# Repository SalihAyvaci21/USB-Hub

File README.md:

# USB Hub + PD Controller Projesi

Bu proje, USB-C PD (Power Delivery) desteği ile çalışan, 5V-24V arası giriş voltajını kabul eden ve gücü dört farklı çıkışa dağıtan bir **USB Hub** tasarımıdır. Güç ve sinyal yönetimi için çeşitli koruma ve anahtarlama IC’leri entegre edilmiştir.

## 📦 Özellikler

- **Giriş Voltajı (USB-C):** 5V - 24V (PD destekli)
- **Çıkışlar:**
  - 1x **USB-A 3.0**
  - 1x **USB-C 3.0**
  - 1x **FTDI (UART-USB dönüştürücü)**
  - 1x **ST-Link (Programlayıcı / Debugger)**
- **PD Controller:** CH224K (Switch ile kontrol)
- **USB Hub IC:** TUSB8044ARGCR
- **Sinyal Yönlendirme:**
  - 2x HD3SS3202IRSVR (SS MUX, C-to-A ve A-to-C için)
- **Koruma Devreleri:**
  - TPD6S300A (ESD ve güç koruması)
- **Güç Regülasyonu:**
  - 1.1V: TLV71211 (SOT23-5)
  - 3.3V: NCP1117-3.3 (SOT-223)
  - 5V: KA78M05 (TO-252)
- **Programlayıcılar:**
  - ST-Link için STM32F103CBTx
  - FTDI için FT232RL-REEL

## 🛠 Bileşenler

| Bileşen                  | Açıklama                        |
|-------------------------|------------------------------------|
| **CH224K**              | USB-C PD Controller              |
| **TUSB8044ARGCR**       | USB 3.0 Hub Controller            |
| **HD3SS3202IRSVR**      | USB SS MUX (C/A anahtarlama)      |
| **TPD6S300A**           | USB-C koruma (ESD, VBUS)          |
| **TLV71211**            | 1.1V LDO Regülatör                |
| **NCP1117-3.3**         | 3.3V LDO Regülatör                |
| **KA78M05**             | 5V Regülatör                      |
| **STM32F103CBTx**       | ST-Link Programlayıcı MCU         |
| **FT232RL-REEL**        | FTDI USB-UART dönüştürücü         |

## 📐 Tasarım Özellikleri

- **PD Desteği:** 5V ila 24V arası giriş voltajını otomatik algılar entegre doğru çıkışı verir.
- **Güç Dağıtımı:** TUSB8044ARGCR ile USB 3.0 sinyalleri dört porta bölünür.
- **Sinyal Yönlendirme:** HD3SS3202 ile USB-C ve USB-A arasında yüksek hızlı sinyal yönlendirme.
- **Güvenlik:** TPD6S300A ile USB-C girişinde aşırı gerilim ve ESD koruması.
- **Programlama ve Debug:** Dahili ST-Link (STM32F103CBTx) ve FTDI (FT232RL) arayüzleri.

## 🔌 Kullanım

1. **Giriş Bağlantısı:**
   - USB-C PD girişine adaptör bağlayın (5V-24V arası desteklenir).
2. **Çıkışlar:**
   - USB-A 3.0 portuna cihaz bağlanabilir.
   - USB-C 3.0 portu yüksek hızlı veri aktarımı için kullanılabilir.
   - FTDI portu UART bağlantısı için kullanılabilir.
   - ST-Link portu STM32 debug/programlama için hazırdır.

## ⚡ Koruma ve Güvenlik

- **ESD Koruma:** TPD6S300A
- **Aşırı Gerilim:** PD kontrolcü ile voltaj sınırlaması
- **Sinyal Integrity:** SS MUX ile minimum sinyal kaybı

## 📁 Dosyalar

- `Usb 3. v11.kicad_pro` – KiCAD proje dosyası
- `Usb 3. v11.kicad_sch` – Devre şeması
- `gerber` – Üretim için Gerber dosyaları 
- `BomList.xlsx` – Parça listesi

## ⚠️ Dikkat

> Bu tasarım yüksek hızlı USB sinyalleri ve PD voltajları içerir. Geliştirme ve test sırasında uygun yalıtım ve ESD önlemleri alınmalıdır.

## 📜 Lisans

Bu proje açık kaynaklıdır ve kişisel/akademik kullanım için serbesttir.

---

# USB Hub + PD Controller Project

This project is a **USB Hub** design that operates with USB-C PD (Power Delivery) support, accepting an input voltage range of 5V-24V and distributing power across four different outputs. Various protection and switching ICs are integrated for power and signal management.

## 📦 Features

- **Input Voltage (USB-C):** 5V - 24V (PD supported)
- **Outputs:**
  - 1x **USB-A 3.0**
  - 1x **USB-C 3.0**
  - 1x **FTDI (UART-USB converter)**
  - 1x **ST-Link (Programmer / Debugger)**
- **PD Controller:** CH224K (controlled via switch)
- **USB Hub IC:** TUSB8044ARGCR
- **Signal Routing:**
  - 2x HD3SS3202IRSVR (SS MUX for C-to-A and A-to-C)
- **Protection Circuits:**
  - TPD6S300A (ESD and power protection)
- **Power Regulation:**
  - 1.1V: TLV71211 (SOT23-5)
  - 3.3V: NCP1117-3.3 (SOT-223)
  - 5V: KA78M05 (TO-252)
- **Programmers:**
  - STM32F103CBTx for ST-Link
  - FT232RL-REEL for FTDI

## 🛠 Components

| Component              | Description                         |
|------------------------|-------------------------------------|
| **CH224K**             | USB-C PD Controller                 |
| **TUSB8044ARGCR**      | USB 3.0 Hub Controller              |
| **HD3SS3202IRSVR**     | USB SS MUX (C/A switching)          |
| **TPD6S300A**          | USB-C protection (ESD, VBUS)        |
| **TLV71211**           | 1.1V LDO Regulator                  |
| **NCP1117-3.3**        | 3.3V LDO Regulator                  |
| **KA78M05**            | 5V Regulator                        |
| **STM32F103CBTx**      | ST-Link Programmer MCU              |
| **FT232RL-REEL**       | FTDI USB-UART Converter             |

## 📐 Design Features

- **PD Support:** Automatically detects input voltage between 5V and 24V and provides appropriate regulated output.
- **Power Distribution:** USB 3.0 signals are distributed to four ports using TUSB8044ARGCR.
- **Signal Routing:** High-speed signal switching between USB-C and USB-A via HD3SS3202.
- **Protection:** Overvoltage and ESD protection on USB-C input using TPD6S300A.
- **Programming and Debugging:** Integrated ST-Link (STM32F103CBTx) and FTDI (FT232RL) interfaces.

## 🔌 Usage

1. **Input Connection:**
   - Connect an adapter to the USB-C PD input (supports 5V-24V).
2. **Outputs:**
   - USB-A 3.0 port can connect to devices.
   - USB-C 3.0 port supports high-speed data transfer.
   - FTDI port can be used for UART connections.
   - ST-Link port is ready for STM32 debugging/programming.

## ⚡ Protection and Safety

- **ESD Protection:** TPD6S300A
- **Overvoltage:** Voltage limitation via PD controller
- **Signal Integrity:** Minimal signal loss using SS MUX

## 📁 Files

- `Usb 3. v11.kicad_pro` – KiCAD project file
- `Usb 3. v11.kicad_sch` – Schematic file
- `gerber` – Gerber files for production
- `BomList.xlsx` – Bill of Materials

## ⚠️ Warning

> This design involves high-speed USB signals and PD voltages. Proper insulation and ESD precautions must be taken during development and testing.

## 📜 License

This project is open-source and free for personal and academic use.

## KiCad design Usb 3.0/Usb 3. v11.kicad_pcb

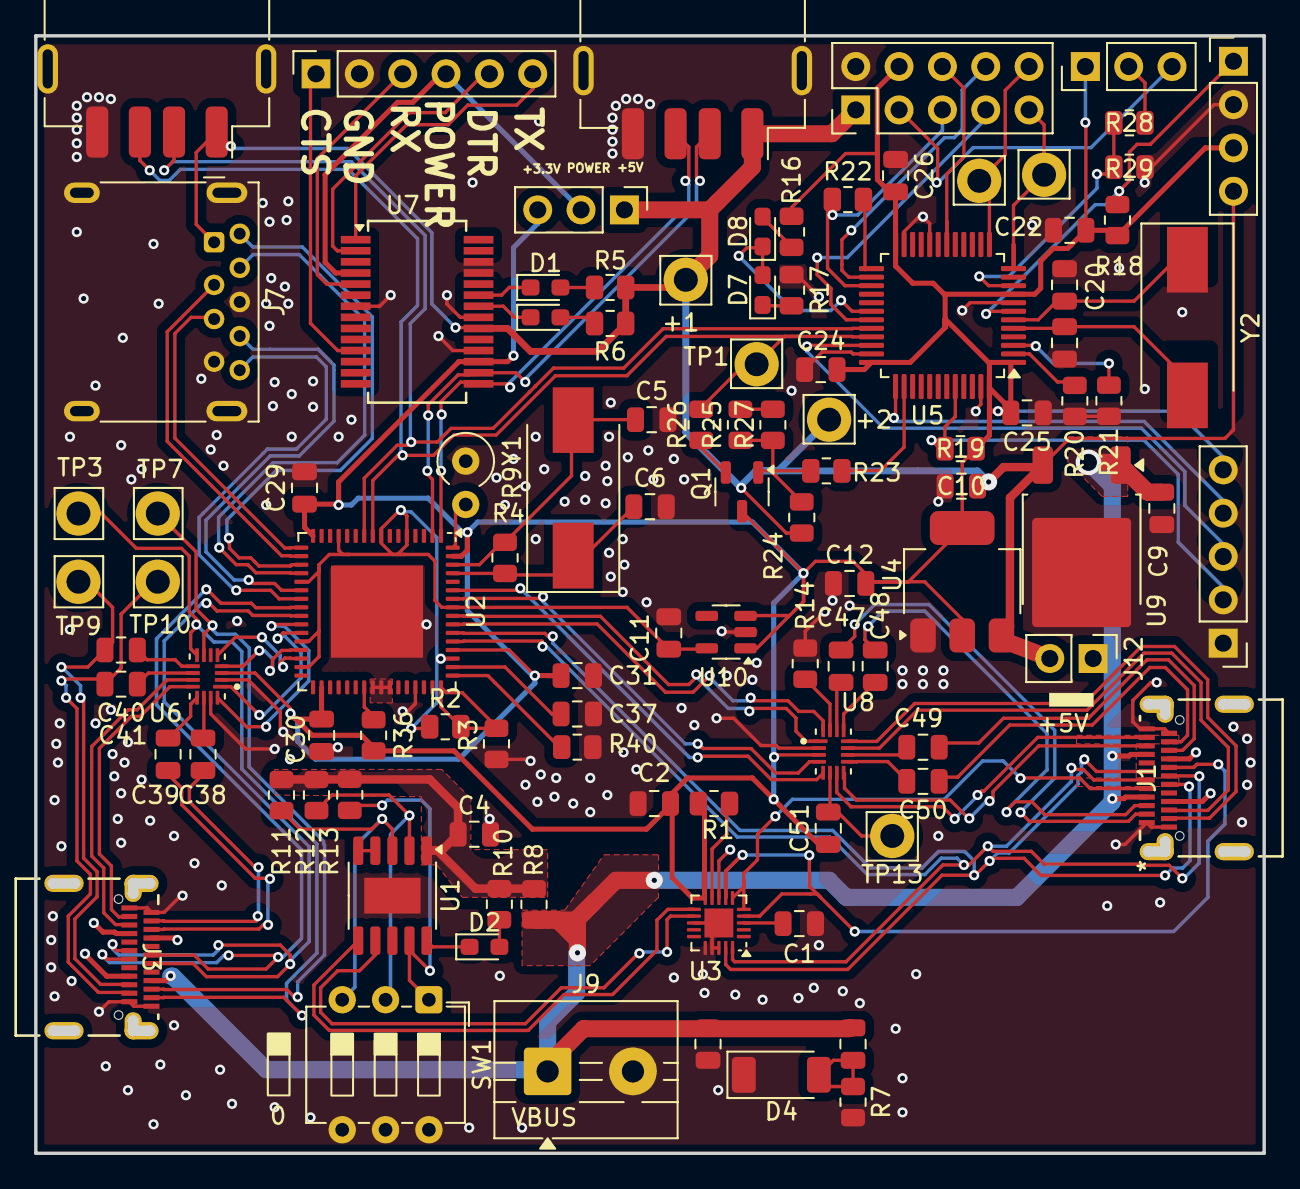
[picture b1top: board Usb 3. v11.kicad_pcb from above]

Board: 2 copper layers, 72.0 x 65.5 mm, 103 parts (0 on the bottom side), 108 nets.

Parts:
+1, +2: TestPoint; Pin_D1.4mm_L8.5mm_W2.8mm_FlatFork
C1, C29, C30, C31, C38, C39, C40, C41, C47, C48, C49, C50, C51: 0.1uF; C_0805_2012Metric
C2, C3, C4, C9, C10, C11, C12: 1uF; C_0805_2012Metric
C5, C6, C19, C20: 20pF; C_0805_2012Metric
C22, C24, C25, C26: 100nF; C_0805_2012Metric
C35: 4.7uF; C_0805_2012Metric
C37: 0.1uf; C_0805_2012Metric
D1, D3, D7, D8: LTST-C190GKT; LED_0603_1608Metric_Pad1.05x0.95mm_HandSolder
D2: LTST-C191KRKT; LED_0603_1608Metric_Pad1.05x0.95mm_HandSolder
D4: D_Schottky /20V/5A; D_SOD-128
J1, J3: KUSBX-SMT-CS2-B30TR; KUSBX-SMT3-CS-BTR_KYC
J2: Conn_01x06; PinSocket_1x06_P2.54mm_Vertical
J4: Conn_01x03_Pin; PinHeader_1x03_P2.54mm_Vertical
J5: Conn_01x05_Pin; PinHeader_1x05_P2.54mm_Vertical
J6: Conn_02x05_Odd_Even; PinHeader_2x05_P2.54mm_Vertical
J7: USB3_A; USB3_A_Molex_48393-001
J8, J10: USB_A; USB_A_Receptacle_GCT_USB1046
J9: Screw_Terminal_01x02; TerminalBlock_MaiXu_MX126-5.0-02P_1x02_P5.00mm
J11: Conn_01x04_Pin; PinHeader_1x04_P2.54mm_Vertical
J12: Screw_Terminal_01x02; PinHeader_1x02_P2.54mm_Vertical
JP1: SolderJumper_3_Open; PinHeader_1x03_P2.54mm_Vertical
Q1: BC817-25-TP; SOT-23-3
R1: 100k; R_0805_2012Metric
R2: 90.9k %1; R_0805_2012Metric
R3: 10k %1; R_0805_2012Metric
R4: 1M; R_0805_2012Metric
R5, R6, R8, R10, R16, R17: 1k; R_0805_2012Metric
R7: 3.5ohm; R_0805_2012Metric
R9: 0.53k %1; R_Axial_DIN0309_L9.0mm_D3.2mm_P2.54mm_Vertical
R11, R12, R13, R14, R18, R19, R36, R40: 10k; R_0805_2012Metric
R20, R21, R24: 10K; R_0805_2012Metric
R22, R23: 100R; R_0805_2012Metric
R25: 39K; R_0805_2012Metric
R26: 1.5k; R_0805_2012Metric
R27: 33K; R_0805_2012Metric
R28, R29: 4.7k; R_0805_2012Metric
SW1: SW_DIP_x03; SW_DIP_SPSTx03_Slide_6.7x9.18mm_W7.62mm_P2.54mm_LowProfile
TP1, TP3, TP5, TP6, TP7, TP9, TP10, TP13: TestPoint; Pin_D1.4mm_L8.5mm_W2.8mm_FlatFork
U1: CH224K; SSOP-10-1EP_3.9x4.9mm_P1mm_EP2.1x3.3mm
U2: TUSB8044ARGCR; VQFN-64-1EP_9x9mm_P0.5mm_EP5.4x5.4mm_ThermalVias
U3: TPD6S300A; WQFN-20-1EP_3x3mm_P0.4mm_EP1.7x1.7mm_ThermalVias
U4: NCP1117-3.3_SOT223; SOT-223-3_TabPin2
U5: STM32F103CBTx; LQFP-48_7x7mm_P0.5mm
U6, U8: HD3SS3202IRSVR; QFN40P180X260X55-16N_HD3SS3202RSVT
U7: FT232RL-REEL; SSOP-28_5.3x10.2mm_P0.65mm
U9: KA78M05_TO252; TO-252-2
U10: TLV71211_SOT23-5; SOT-23-5
Y1: 24Mhz; Crystal_SMD_EuroQuartz_MQ2-2Pin_7.0x5.0mm_HandSoldering
Y2: 8Mhz; Crystal_SMD_EuroQuartz_MQ2-2Pin_7.0x5.0mm_HandSoldering

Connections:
1.1v: C11.2, R2.1, U2.5 (VDD), U2.8 (VDD), U2.13 (VDD), U2.21 (VDD), U2.28 (VDD), U2.31 (VDD), U2.51 (VDD), U2.57 (VDD), U10.5 (OUT)
+3.3V: C2.1, C12.2, C22.2, C24.2, C25.2, C26.2, C29.1, C30.1, C31.1, C51.1, J4.1, J5.5, J6.4, J11.3, JP1.3 (B), Q1.3 (C), R1.1, R16.2, R18.1, R19.1, R36.1, U2.16 (VDD33), U2.34 (VDD33), U2.52 (VDD33), U2.63 (VDD33), U3.10 (VPWR), U4.2 (VO), U5.1 (VBAT), U5.9 (VDDA), U5.24 (VDD), U5.36 (VDD), U5.48 (VDD), U6.3 (VCC), U7.17 (3V3OUT), U8.3 (VCC), U10.1 (IN), U10.3 (EN)
+5V: +1.1, +2.1, C10.2, J6.1, J7.1 (VBUS), J8.1 (VBUS), J10.1 (VBUS), J11.4, J12.2, JP1.1 (A), R5.1, R6.1, R24.1, U4.3 (VI), U7.20 (VCC), U9.3 (VO)
/FTDI/POWER: J2.4, JP1.2 (C), U7.4 (VCCIO)
/ST-Link V2/BOOT0: J5.2, R19.2, U5.44 (BOOT0)
/ST-Link V2/CLK: J5.4, U5.37 (PA14)
/ST-Link V2/DIO: J5.3, U5.34 (PA13)
/ST-Link V2/LED: D7.2, D8.1, U5.30 (PA9)
/ST-Link V2/RENUM: R23.2, U5.38 (PA15)
/ST-Link V2/RX: J6.10, TP6.1, U5.13 (PA3)
/ST-Link V2/TX: J6.9, TP5.1, U5.12 (PA2)
/ST-Link V2/T_CLK: J6.8, U5.26 (PB13)
/ST-Link V2/T_DIO: J6.5, R22.1, U5.27 (PB14)
/ST-Link V2/T_NRST: J6.6, U5.18 (PB0)
/ST-Link V2/T_PWR: J4.3, J6.3
/ST-Link V2/T_SWO: J6.7, U5.31 (PA10)
/ST-Link V2/X0: C20.2, U5.6 (PD1), Y2.1
/ST-Link V2/XI: C19.2, U5.5 (PD0), Y2.2
/esdprotection/+: C47.1, J1.A2 (SSTXP1)
/esdprotection/-: C48.1, J1.A3 (SSTXN1)
CFG1: R13.2, SW1.1, U1.9 (CFG1)
CFG2: R12.2, SW1.2, U1.2 (CFG2)
CFG3: R11.2, SW1.3, U1.3 (CFG3)
CTS: J2.1, U7.11 (CTS)
D1N: J8.2 (D-), U2.2 (USB_DM_DN1), U7.16 (USBDM)
D1P: J8.3 (D+), U2.1 (USB_DP_DN1), U7.15 (USBDP)
D2N: J10.2 (D-), U2.10 (USB_DM_DN2), U5.32 (PA11)
D2P: J10.3 (D+), R26.2, TP1.1, U2.9 (USB_DP_DN2), U5.33 (PA12)
D3N: J7.2 (D-), U2.18 (USB_DM_DN3)
D3P: J7.3 (D+), U2.17 (USB_DP_DN3)
D4N: J3.A7 (DN1), J3.B7 (DN2), U2.25 (USB_DM_DN4)
D4P: J3.A6 (DP1), J3.B6 (DP2), U2.24 (USB_DP_DN4)
DN3_RXN: J7.5 (SSRX-), U2.23 (USB_SSRXM_DN3)
DN3_RXP: J7.6 (SSRX+), U2.22 (USB_SSRXP_DN3)
DN3_TXN: J7.8 (SSTX-), U2.20 (USB_SSTXM_DN3)
DN3_TXP: J7.9 (SSTX+), U2.19 (USB_SSTXP_DN3)
DN4_RXN: U2.30 (USB_SSRXM_DN4), U6.5 (A1N)
DN4_RXP: U2.29 (USB_SSRXP_DN4), U6.4 (A1P)
DN4_TXN: U2.27 (USB_SSTXM_DN4), U6.1 (A0N)
DN4_TXP: U2.26 (USB_SSTXP_DN4), U6.16 (A0P)
DTR: J2.5, U7.2 (DTR)
D_N: J1.A7 (DN1), J1.B7 (DN2), U2.54 (USB_DM_UP), U3.19 (D2)
D_P: J1.A6 (DP1), J1.B6 (DP2), U2.53 (USB_DP_UP), U3.20 (D1)
FTDI-RX: J2.3, U7.5 (RXD)
FTDI-TX: J2.6, U7.1 (TXD)
GNDREF: C1.1, C2.2, C3.2, C4.2, C5.2, C6.2, C9.1, C10.1, C11.1, C12.1, C19.1, C20.1, C22.1, C24.1, C25.1, C26.1, C29.2, C30.2, C31.2, C37.2, D4.1 (K), J1.A1 (GND), J1.A12 (GND), J1.B1 (GND), J1.B12 (GND), J2.2, J3.A1 (GND), J3.A12 (GND), J3.B1 (GND), J3.B12 (GND), J5.1, J6.2, J7.4 (GND), J7.7 (DRAIN), J7.10 (SHIELD), J8.4 (GND), J8.5 (Shield), J9.2, J10.4 (GND), J10.5 (Shield), J11.2, R3.1, R7.2, R9.1, R14.2, R17.1, R20.1, R21.1, R29.2, R40.2, SW1.4, SW1.5, SW1.6, U1.11 (GND), U2.40 (BBbmConfigured0_FULLAUTO_FULLPWRMGMT_SS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), U2.41 (PWRCTL_POL), U2.42 (BBEN_GANGED_HS_UP), U2.45 (BBbmConfigured1_AUTOENz_HS_SUSPEND), U2.65 (PAD), U3.8 (GND), U3.13 (GND), U3.16 (GND), U3.17 (GND), U3.18 (GND), U3.21 (GND), U4.1 (GND), U5.8 (VSSA), U5.20 (PB2), U5.23 (VSS), U5.35 (VSS), U5.47 (VSS), U6.2 (GND), U6.15 (OEN), U7.7 (GND), U7.18 (GND), U7.21 (GND), U7.25 (AGND), U7.26 (TEST), U8.2 (GND), U9.2 (GND), U10.2 (GND)
NRST: J11.1, R18.2, U5.7 (NRST)
unnamed: D1.2, R5.2
unnamed: D2.2, R10.1
unnamed: D3.2, R6.2
unnamed: C35.2, D4.2 (A), R7.1
unnamed: D7.1, R17.2
unnamed: D8.2, R16.1
unnamed: J1.A5 (CC1), U3.5 (C_CC2), U3.6 (RPD_G2)
unnamed: J1.B5 (CC2), U3.4 (C_CC1), U3.7 (RPD_G1)
unnamed: C49.1, J1.B3 (SSTXN2)
unnamed: C50.1, J1.B2 (SSTXP2)
unnamed: J4.2, R28.1
unnamed: Q1.1 (B), R23.1, R24.2, R25.1, R27.1
unnamed: Q1.2 (E), R26.1
unnamed: R25.2, R27.2
unnamed: U1.4 (DP), U1.5 (DM)
unnamed: D2.1, U1.10 (PG)
unnamed: C37.1, U2.50 (GRST_N)
unnamed: R36.2, U2.39 (SMBUS_SS_SUSPEND_N)
unnamed: R40.1, U2.49 (TEST)
unnamed: R9.2, U2.64 (USB_R1)
unnamed: R2.2, R3.2, U2.48 (USB_VBUS)
unnamed: C5.1, R4.1, U2.62 (XI), Y1.2
unnamed: C6.1, R4.2, U2.61 (XO), Y1.1
unnamed: C1.2, U3.3 (VBIAS)
unnamed: R1.2, U3.9 (~FLT)
unnamed: R28.2, R29.1, U5.10 (PA0)
unnamed: R22.2, U5.25 (PB12)
unnamed: R20.2, U5.2 (PC13)
unnamed: R21.2, U5.3 (PC14)
unnamed: C39.1, U6.13 (B0N)
unnamed: C38.1, U6.14 (B0P)
unnamed: C41.1, U6.9 (C0N)
unnamed: C40.1, U6.10 (C0P)
unnamed: D1.1, U7.23 (CBUS0)
unnamed: D3.1, U7.22 (CBUS1)
unnamed: R14.1, U8.15 (OEN)
unnamed: C51.2, TP13.1, U8.6 (SEL)
PD_CC1: U1.7 (CC1), U3.12 (CC1)
PD_CC2: U1.6 (CC2), U3.11 (CC2)
RX1+: U2.58 (USB_SSRXP_UP), U8.4 (A1P)
RX1-: U2.59 (USB_SSRXM_UP), U8.5 (A1N)
RX1A+: J1.B11 (SSRXP1), U8.12 (B1P)
RX1A-: J1.B10 (SSRXN1), U8.11 (B1N)
RX1N: J3.B10 (SSRXN1), U6.11 (B1N)
RX1P: J3.B11 (SSRXP1), U6.12 (B1P)
RX2A+: J1.A11 (SSRXP2), U8.7 (C1N)
RX2A-: J1.A10 (SSRXN2), U8.8 (C1P)
RX2N: J3.A10 (SSRXN2), TP7.1, U6.7 (C1N)
RX2P: J3.A11 (SSRXP2), TP3.1, U6.8 (C1P)
TX1+: U2.55 (USB_SSTXP_UP), U8.16 (A0P)
TX1-: U2.56 (USB_SSTXM_UP), U8.1 (A0N)
TX1A_N: C48.2, U8.13 (B0N)
TX1A_P: C47.2, U8.14 (B0P)
TX1N: C39.2, J3.A3 (SSTXN1)
TX1P: C38.2, J3.A2 (SSTXP1)
TX2A+: C50.2, U8.9 (C0N)
TX2A-: C49.2, U8.10 (C0P)
TX2N: C41.2, J3.B3 (SSTXN2), TP9.1
TX2P: C40.2, J3.B2 (SSTXP2), TP10.1
VBUS: C3.1, C9.2, C35.1, J1.A4 (VBUS), J1.A9 (VBUS), J1.B4 (VBUS), J1.B9 (VBUS), J3.A4 (VBUS), J3.A9 (VBUS), J3.B4 (VBUS), J3.B9 (VBUS), J9.1, J12.1, R8.1, U9.1 (VI)
VDD: C4.1, R8.2, R10.2, R11.1, R12.1, R13.1, U1.1 (VDD)

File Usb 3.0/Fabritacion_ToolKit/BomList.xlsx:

Reference | Value | Digi-Key_PN | MPN | Qty | Supplier | Footprint
C1,C29,C30,C31,C38,C39,C40,C41,C47,C48,C49,C50,C51 | 0.1uF | 399-C0805C104M5RACTUTR-ND | C0805C104M5RACTU | 13 | digikey | Capacitor_SMD:C_0805_2012Metric
C2,C3,C4,C9,C10,C11,C12,C13 | 1uF | 1276-1066-2-ND | CL21B105KAFNNNE | 7 | digikey | Capacitor_SMD:C_0805_2012Metric
C5,C6,C19,C20 | 20pF | 399-C0805C180J5HACTUTR-ND | C0805C180J5HACTU | 2 | digikey | Capacitor_SMD:C_0805_2012Metric
 |  | 399-C0805C180J5HACTUTR-ND | C0805C180J5HACTU | 2 | digikey | Capacitor_SMD:C_0805_2012Metric
C22,C24,C25,C26 | 100nF | 2679-C0805X5R100-104KNE-CT-ND | C0805X5R100-104KNE-CT | 4 | digikey | Capacitor_SMD:C_0805_2012Metric
C35 | 4.7uF | 1276-1244-2-ND | CL21A475KAQNNNE | 1 | digikey | Capacitor_SMD:C_0805_2012Metric
C37 | 0.1uf | 311-1344-2-ND | CC0603KRX7R9BB104 | 1 | digikey | Capacitor_SMD:C_0805_2012Metric
D1,D3,D7,D8 | LTST-C190GKT | 160-1183-1-ND | LTST-C190GKT | 4 | digikey | LED_SMD:LED_0603_1608Metric_Pad1.05x0.95mm_HandSolder
D2 | LTST-C191KRKT | 160-1447-1-ND | LTST-C191KRKT | 1 | digikey | LED_SMD:LED_0603_1608Metric_Pad1.05x0.95mm_HandSolder
D4 | D_Schottky /20V/5A | RB081LAM-20TRTR-ND | RB081LAM-20TR | 1 | digikey | Diode_SMD:D_SOD-128
J1,J3 | KUSBX-SMT-CS2-B30TR | 2092-KUSBX-SMT-CS2-B30TR-ND | KUSBX-SMT-CS2-B30TR | 2 | digikey | KUSBX-SMT3-CS-BTR_KYC
J2 | Conn_01x06 | 2553-2044-1X06G00SB-ND | 2044-1X06G00SB | 1 | digikey | Connector_PinSocket_2.54mm:PinSocket_1x06_P2.54mm_Vertical
J6 | Conn_02x05_Odd_Even | 2553-2044-2X05G00SB-ND | 2044-2X05G00SB | 1 | digikey | Connector_PinSocket_1.27mm:PinSocket_2x05_P1.27mm_Vertical
J7 | USB3_A | GSB316441CEUTR-ND | GSB316441CEU | 1 | digikey | Connector_USB:USB3_A_Molex_48393-001
J8,J10 | USB_A | 2987-CU01SAV0S00-ND | CU01SAV0S00
J9 | Screw_Terminal_01x02 | 5831-1715330000-ND | 1715330000 | 1 | digikey | TerminalBlock:TerminalBlock_MaiXu_MX126-5.0-02P_1x02_P5.00mm
Q1 | BC817-25-TP | BC817-25-TPMSCT-ND | BC817-25-TP | 1 | digikey | Package_TO_SOT_SMD:SOT-23-3
R1 | 100k | 311-100KCRTR-ND | RC0805FR-07100KL | 1 | digikey | Resistor_SMD:R_0805_2012Metric
R2 | 90.9k %1 | 311-90.9KCRTR-ND | RC0805FR-0790K9L | 1 | digikey | Resistor_SMD:R_0805_2012Metric
R3 | 10k %1 | 311-10.0KLRCT-ND | RC0805FR-0710KL | 1 | digikey | Resistor_SMD:R_0805_2012Metric
R4 | 1M | 311-1.0MARTR-ND | RC0805JR-071ML | 1 | digikey | Resistor_SMD:R_0805_2012Metric
R5,R6,R8,R10,R16,R17 | 1k | 311-1.00KCRTR-ND | RC0805FR-071KL | 6 | digikey | Resistor_SMD:R_0805_2012Metric
R7 | 3.5ohm | P3.57KLTR-ND | ERJ-2RKF3571X | 1 | digikey | Resistor_SMD:R_0805_2012Metric
R9 | 0.53k %1 | 2019-RN73R1JTTD5300F100TR-ND | RN73R1JTTD5300F100 | 1 | digikey | Resistor_SMD:R_0805_2012Metric
R11,R12,R13,R14,R18,R19,R36,R40,R20,R21,R24 | 10k | 311-10.0KCRTR-ND | RC0805FR-0710KL | 11 | digikey | Resistor_SMD:R_0805_2012Metric
R20, R21,R24 | 100R | 311-100CRTR-ND | RC0805FR-07100RL | 2 | digikey | Resistor_SMD:R_0805_2012Metric
R25 | 39K | 311-39.0KCRTR-ND | RC0805FR-0739KL | 1 | digikey | Resistor_SMD:R_0805_2012Metric
R26 | 1.5K | RHM1.5KTR-ND | ESR10EZPJ1R5 | 1 | digikey | Resistor_SMD:R_0805_2012Metric
SW1 | SW_DIP_x03 | CT2093MS-ND | 209-3MS | 1 | digikey | Button_Switch_THT:SW_DIP_SPSTx03_Slide_6.7x9.18mm_W7.62mm_P2.54mm_LowProfile
SW2,SW3 | SW_Omron_B3FS | CKN12222-2-ND | PTS526SMG15SMTR2 LFS | 2 | digikey | Button_Switch_SMD:SW_SPST_Omron_B3FS-100xP
TP1,TP2,TP3,TP4,TP5,TP6,TP7,TP8,TP9,TP10,TP11,TP12,TP13 | TestPoint |  |  | 13 | digikey | Connector_Pin:Pin_D1.4mm_L8.5mm_W2.8mm_FlatFork
U1 | CH224K | A0641 | PD/QC/AFC Hızlı Şarj Tetikleme Modülü | 1 | robotronik | Package_SO:SSOP-10-1EP_3.9x4.9mm_P1mm_EP2.1x3.3mm
U2 | TUSB8044ARGCR | 296-53620-2-ND | TUSB8044ARGCR | 1 | digikey | Package_DFN_QFN:VQFN-64-1EP_9x9mm_P0.5mm_EP5.4x5.4mm_ThermalVias
U3 | TPD6S300A | 296-51856-2-ND | TPD6S300ARUKR | 1 | digikey | Package_DFN_QFN:WQFN-20-1EP_3x3mm_P0.4mm_EP1.7x1.7mm_ThermalVias
U4 | NCP1117-3.3_SOT223 | 863-NCP1117LPST33T3G | NCP1117LPST33T3G | 1 | digikey | Package_TO_SOT_SMD:SOT-223-3
U5 | STM32F103CBTx | 497-17380-2-ND | STM32F103CBT6TR | 1 | digikey | Package_QFP:LQFP-48_7x7mm_P0.5mm
U6,U8 | HD3SS3202IRSVR | 296-HD3SS3202IRSVRTR-ND | HD3SS3202IRSVR | 2 | digikey | Package_DFN_QFN:UQFN-16-1EP_4x4mm_P0.65mm_EP2.6x2.6mm_ThermalVias
U7 | FT232RL-REEL | 768-1007-1-ND | FT232RL-REEL | 1 | digikey | Package_SO:SSOP-28_5.3x10.2mm_P0.65mm
U9 | KA78M05_TO252 | 511-L7805CDT-TR | L7805CDT-TR | 1 | digikey | Package_TO_SOT_SMD:TO-252-2
U10 | TLV71211_SOT23-5 | 296-30593-2-ND | TLV71211DBVR | 1 | digikey | Package_TO_SOT_SMD:SOT-23-5
XTAL1 | 16Mhz | 535-12830-2-ND | ABLS7M2-16.000MHZ-D2Y-T | 1 | digikey | Crystal:Crystal_SMD_EuroQuartz_EQ161-2Pin_3.2x1.5mm_HandSoldering
Y1 | 24Mhz | ABLS7M2-24.000MHZ-D2Y-T | ABLS7M2-24.000MHZ-D2Y-T | 1 | digikey | Crystal:Crystal_SMD_EuroQuartz_MQ2-2Pin_7.0x5.0mm_HandSoldering

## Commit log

2025-07-18 README.md
